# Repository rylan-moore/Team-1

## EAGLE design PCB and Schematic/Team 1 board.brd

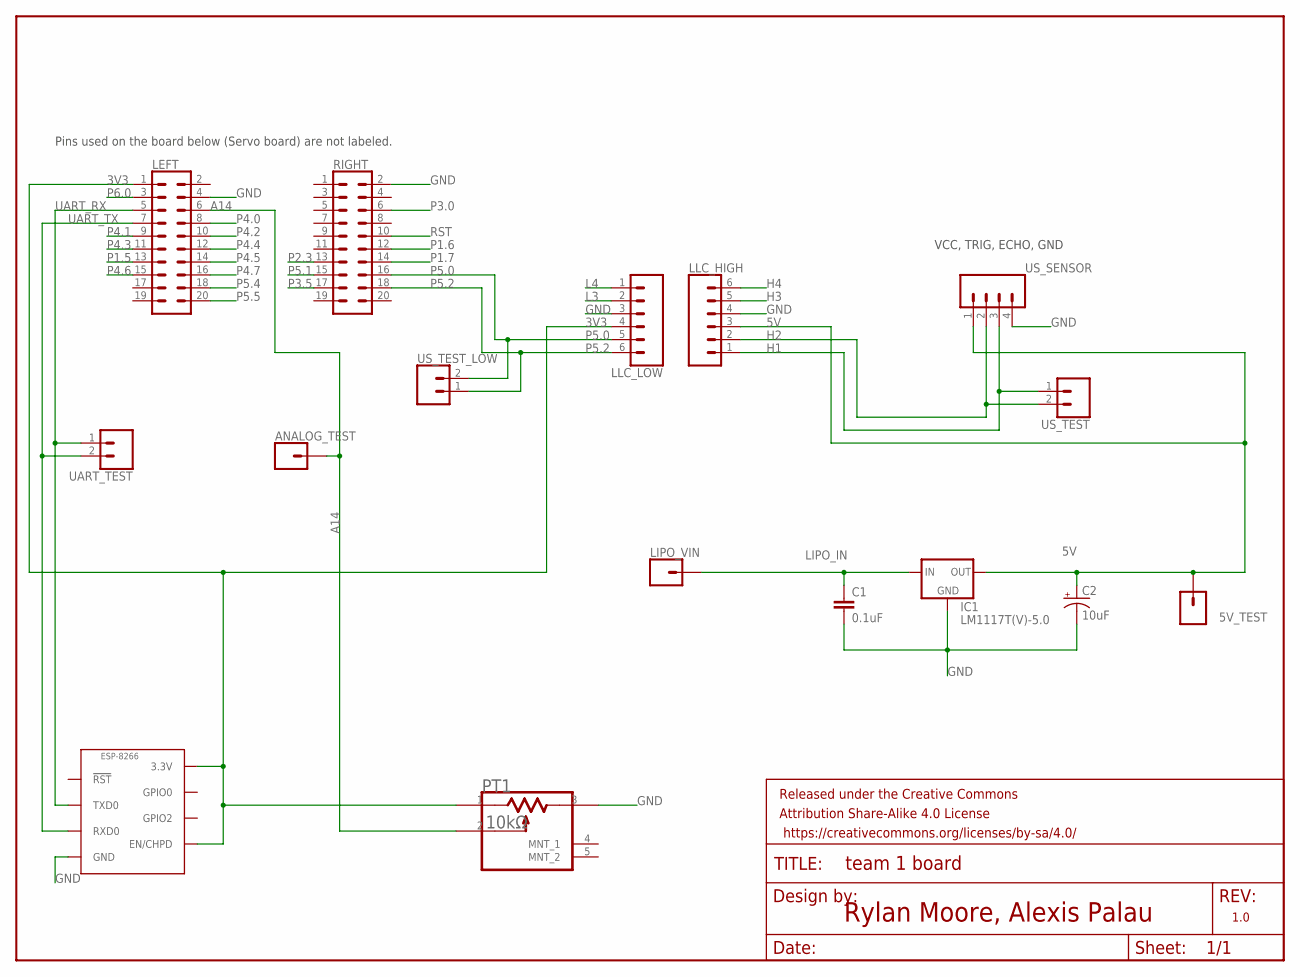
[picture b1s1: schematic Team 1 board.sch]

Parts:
5V_TEST: CONN_01; 1X01
ANALOG_TEST: CONN_01; 1X01
C1: 0.1uF; CAP-PTH-SMALL-KIT
C2: 10uF; CPOL-RADIAL-2.5MM-5MM
ESP-8266: ESP8266_ESP-01; ESP8266_ESP-01_NO-SILKSCREEN
FRAME1: FRAME-LETTERNO_PACKAGE; DUMMY
IC1: LM1117T(V)-5.0; TO220V
LEFT: CONN_10X2NOSILK; 2X10_NOSILK
LIPO_VIN: CONN_01; 1X01
LLC_HIGH: CONN_06SILK_FEMALE_PTH; 1X06
LLC_LOW: CONN_06SILK_FEMALE_PTH; 1X06
PT1: ECG_EVU-F2AF30B14ECG_EVU-F2AF30B14_0_0; ECG_EVU-F2AF30B14_0
RIGHT: CONN_10X2NOSILK; 2X10_NOSILK
UART_TEST: CONN_02; 1X02
US_SENSOR: CONN_04; 1X04
US_TEST: CONN_02; 1X02
US_TEST_LOW: CONN_02; 1X02

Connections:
3V3: ESP-8266.3V3 (3.3V), ESP-8266.EN/CH_PD (EN/CHPD), LEFT.1, LLC_LOW.4, PT1.1
5V: 5V_TEST.1, C2.1 (+), IC1.2 (OUT), LLC_HIGH.3, US_SENSOR.1
A14: ANALOG_TEST.1, LEFT.6, PT1.2
GND: C1.2, C2.2 (-), ESP-8266.GND, IC1.1 (GND), LEFT.4, LLC_HIGH.4, LLC_LOW.3, PT1.3, RIGHT.2, US_SENSOR.4
H1: LLC_HIGH.1, US_SENSOR.3, US_TEST.1
H2: LLC_HIGH.2, US_SENSOR.2, US_TEST.2
H3: LLC_HIGH.5
H4: LLC_HIGH.6
L3: LLC_LOW.2
L4: LLC_LOW.1
LIPO_IN: C1.1, IC1.3 (IN), LIPO_VIN.1
P1.5: LEFT.13
P1.6: RIGHT.12
P1.7: RIGHT.14
P2.3: RIGHT.13
P3.0: RIGHT.6
P3.5: RIGHT.17
P4.0: LEFT.8
P4.1: LEFT.9
P4.2: LEFT.10
P4.3: LEFT.11
P4.4: LEFT.12
P4.5: LEFT.14
P4.6: LEFT.15
P4.7: LEFT.16
P5.0: LLC_LOW.5, RIGHT.16, US_TEST_LOW.2
P5.1: RIGHT.15
P5.2: LLC_LOW.6, RIGHT.18, US_TEST_LOW.1
P5.4: LEFT.18
P5.5: LEFT.20
P6.0: LEFT.3
RST: RIGHT.10
UART_RX: ESP-8266.TX (TXD0), LEFT.5, UART_TEST.1
UART_TX: ESP-8266.RX (RXD0), LEFT.7, UART_TEST.2

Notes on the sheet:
Rylan Moore, Alexis Palau
1.0
VCC, TRIG, ECHO, GND
Pins used on the board below (Servo board) are not labeled.

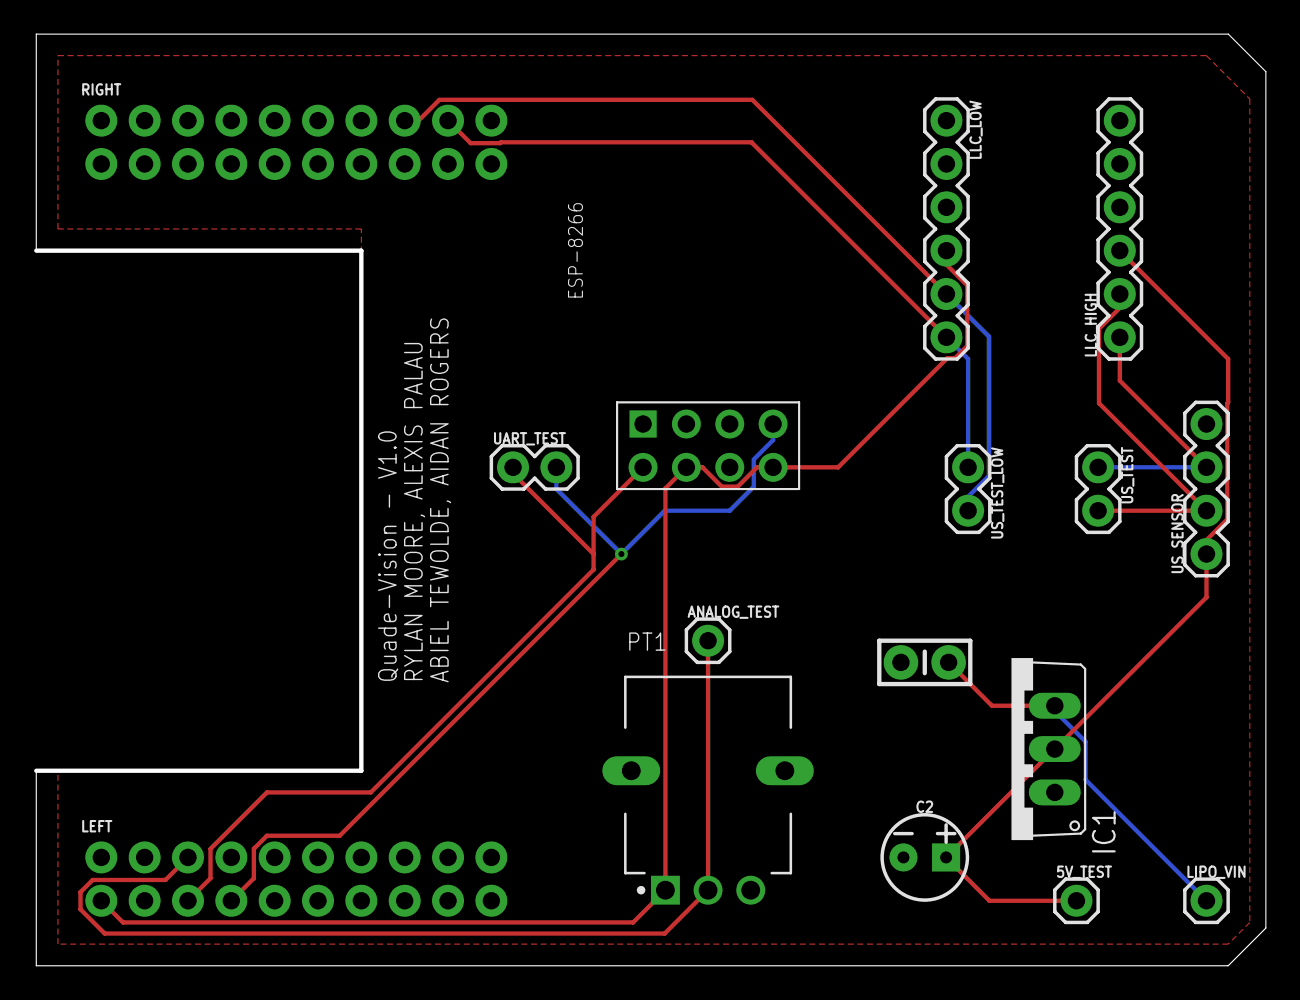
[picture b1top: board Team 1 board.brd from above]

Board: 2 copper layers, 71.9 x 54.3 mm, 17 parts (0 on the bottom side), 11 nets.

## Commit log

2020-11-02 test
2020-11-04 First add of the US sensor
    Ultrasonic sensor code
2020-11-04 Test editing
2020-11-05 potentiometer setup and basic test
2020-11-06 jx commit
2020-11-16 Integrates servos, US, and potentiometer
2020-11-16 Updated to Timer A1
2020-11-18 First build of the final code. Needs state machine, ESP 8266, and Quade updates
2020-11-18 Updated with separated files
2020-11-18 Updated with bettter main.c information
2020-12-02 Final github push
2020-12-05 Commit for final upload
    This commit contains Eagle files, technical documents, and the final code with the updated state machine and UART baud rate changed to that of the wifi module.
    -WIFI module is not implemented!
    -Quade components are not included due to lack of componets required to make quade function.
2020-12-05 Next update
    This commit includes:
    Better comments and descriptions
    UART message over GPIO 3.3 (would comm. with ESP 8266 in future if implemented)

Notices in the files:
parts and their libraries:
SparkFun-Capacitors: Licensing: Creative Commons ShareAlike 4.0 International - https://creativecommons.org/licenses/by-sa/4.0
SparkFun-Aesthetics: Released under the Creative Commons Attribution Share-Alike 4.0 License
SparkFun-Aesthetics: https://creativecommons.org/licenses/by-sa/4.0
